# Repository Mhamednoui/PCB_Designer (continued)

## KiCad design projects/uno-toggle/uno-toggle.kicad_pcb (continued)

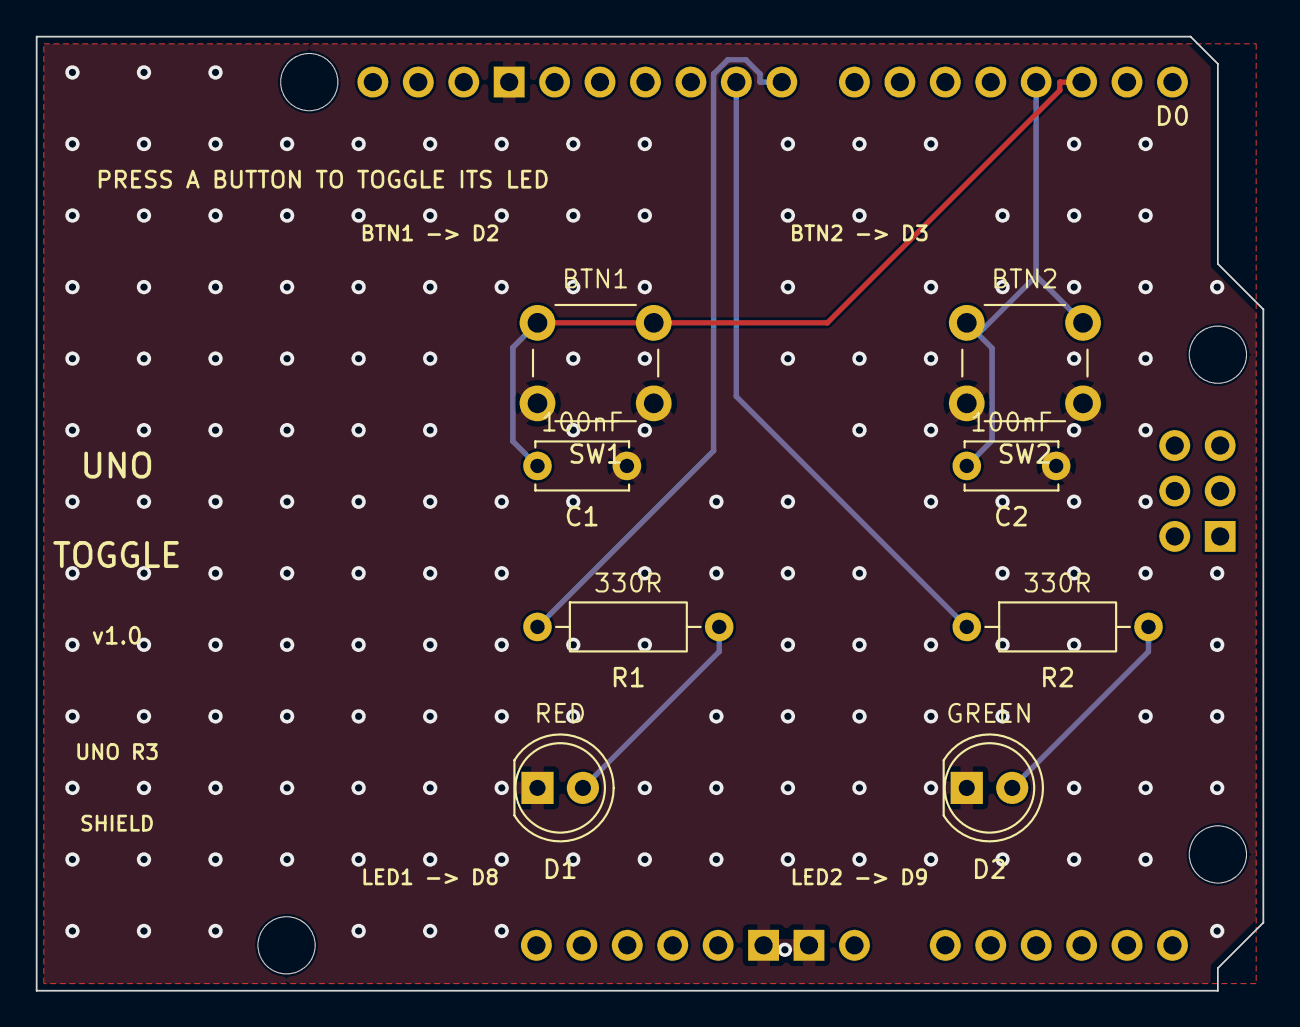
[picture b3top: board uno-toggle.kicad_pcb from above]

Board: 2 copper layers, 68.6 x 53.3 mm, 9 parts (0 on the bottom side), 7 nets.

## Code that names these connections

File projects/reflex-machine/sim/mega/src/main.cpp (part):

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
// -- LED PINS
// 74HC595 shift register driving the 7-segment digit (reuses old mux pins)
#define SEG_DATA   A0   // DS    (serial data)
#define SEG_LATCH  A1   // ST_CP (storage/latch clock)
#define SEG_CLOCK  A2   // SH_CP (shift clock)
const int LED1 = A3;   // STATE_RESET
const int LED2 = A4;   // STATE_RELEASING + last STATE_SPEED_1
const int LED3 = A5;   // STATE_RELEASING + last STATE_SPEED_2
const int LED4 = A6;   // STATE_RELEASING + last STATE_SPEED_3

// ── PWM Output Pins ───────────────────────────────────────
const uint8_t PWM_PINS[10] = { 3, 5, 6, 7, 8, 9, 10, 11, 12, 44 };
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// QC (bit 5) -> f   (top left)
// QB (bit 6) -> g   (middle)
// QA (bit 7) -> NOT CONNECTED
#define SEG_A 0b00010000  // QD bit4
#define SEG_B 0b00000010  // QG bit1
#define SEG_C 0b00000100  // QF bit2
#define SEG_D 0b00000001  // QH bit0
#define SEG_E 0b00001000  // QE bit3
#define SEG_F 0b00100000  // QC bit5
#define SEG_G 0b01000000  // QB bit6

// Common-cathode: a set bit lights its segment.
static const uint8_t SEG_DIGITS[10] = {
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  }

  // 74HC595 control pins
  pinMode(SEG_DATA,  OUTPUT);
  pinMode(SEG_CLOCK, OUTPUT);
  pinMode(SEG_LATCH, OUTPUT);
  pinMode(LED1, OUTPUT);
  pinMode(LED2, OUTPUT);
  pinMode(LED3, OUTPUT);
  pinMode(LED4, OUTPUT);
  allLedsOff();

  for (auto& b : buttons) {
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
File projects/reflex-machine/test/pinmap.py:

"""Cross-check: firmware pins  <->  PCB netlist  <->  board nets.

Reads the pin numbers straight out of the two .cpp files and compares them with gen/netlist.py,
so a wiring/firmware mismatch cannot slip through silently.
"""
import os
import re
import sys

HERE = os.path.dirname(os.path.abspath(__file__))
PRJ = os.path.dirname(HERE)
sys.path.insert(0, os.path.join(PRJ, "gen"))
import netlist as NL  # noqa: E402

MEGA_SRC = os.path.join(os.path.dirname(os.path.dirname(PRJ)), "CODES", "arduino_main_code.cpp")
ESP_SRC = os.path.join(os.path.dirname(os.path.dirname(PRJ)), "CODES", "ESP32_main_code.cpp")


def read(path):
    with open(path, encoding="utf-8", errors="replace") as f:
        return f.read()


def firmware_pins():
    src = read(MEGA_SRC)
    pins = {}
    m = re.search(r"PWM_PINS\[\d+\]\s*=\s*\{([^}]*)\}", src)
    for i, num in enumerate(n.strip() for n in m.group(1).split(",")):
        pins["MAG%d_PWM" % (i + 1)] = "D" + num
    for name, net in (("BTN_SPEED1", "BTN_S1"), ("BTN_SPEED2", "BTN_S2"), ("BTN_SPEED3", "BTN_S3"),
                      ("BTN_RESET", "BTN_RST"), ("COIN_PIN", "COIN_IN")):
        pins[net] = "D" + re.search(r"#define\s+%s\s+(\d+)" % name, src).group(1)
    for name, net in (("SEG_DATA", "SEG_DATA"), ("SEG_LATCH", "SEG_LATCH"), ("SEG_CLOCK", "SEG_CLOCK")):
        pins[net] = re.search(r"#define\s+%s\s+(A\d)" % name, src).group(1)
    for k in range(1, 5):
        pins["LED%d" % k] = re.search(r"const int LED%d\s*=\s*(A\d)" % k, src).group(1)
    pins["MEGA_TX1"] = "D18"      # Serial1 on the Mega is fixed in hardware
    pins["ESP_TX2"] = "D19"
    esp = read(ESP_SRC)
    esp_pins = {"ESP_RX2": int(re.search(r"#define\s+RX2_PIN\s+(\d+)", esp).group(1)),
                "ESP_TX2": int(re.search(r"#define\s+TX2_PIN\s+(\d+)", esp).group(1))}
    return pins, esp_pins


def board_pins():
    mega = next(p for p in NL.PARTS if p["ref"] == "A1")
    esp = next(p for p in NL.PARTS if p["ref"] == "A2")
    return ({net: pad for pad, net in mega["pins"].items()},
            {net: pad for pad, net in esp["pins"].items()})


ESP_PAD_TO_GPIO = {"25": 16, "24": 17, "6": 32, "7": 33, "8": 25, "9": 26, "10": 27, "11": 14}


def main():
    fw, fw_esp = firmware_pins()
    board, board_esp = board_pins()
    rows, bad = [], 0
    for net in sorted(fw, key=lambda n: (n.split("_")[0], n)):
        want, got = fw[net], board.get(net, "-- missing --")
        ok = want == got
        bad += not ok
        rows.append("%-12s firmware %-5s board %-12s %s" % (net, want, got, "OK" if ok else "<-- MISMATCH"))
    for net, gpio in fw_esp.items():
        pad = board_esp.get(net)
        got = ESP_PAD_TO_GPIO.get(pad)
        ok = got == gpio
        bad += not ok
        rows.append("%-12s firmware GPIO%-2s board pin %-3s (GPIO%s) %s"
                    % (net, gpio, pad, got, "OK" if ok else "<-- MISMATCH"))
    print("\n".join(rows))
    print("\n%d signals checked, %d mismatches" % (len(rows), bad))
    return 1 if bad else 0


if __name__ == "__main__":
    sys.exit(main())

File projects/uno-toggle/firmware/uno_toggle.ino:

/*
  Uno Toggle - two buttons, two LEDs.

  Press BTN1 -> LED1 toggles on/off.  Press BTN2 -> LED2 toggles on/off.

  Pin map MUST match gen/netlist.py (test/pinmap.py checks this automatically):
    BTN1 = D2   BTN2 = D3      buttons to GND, internal pull-ups => pressed reads LOW
    LED1 = D8   LED2 = D9      each via 330R to the LED anode, cathode to GND

  Debounce: the board has a 100nF across each switch, and this sketch additionally ignores any edge
  within DEBOUNCE_MS of the last accepted one. Belt and braces - mechanical switches are noisy.
*/

const uint8_t BTN1 = 2;
const uint8_t BTN2 = 3;
const uint8_t LED1 = 8;
const uint8_t LED2 = 9;

const unsigned long DEBOUNCE_MS = 25;

struct Toggle {
  uint8_t buttonPin;
  uint8_t ledPin;
  bool ledOn;
  int lastReading;
  unsigned long lastChangeMs;
};

Toggle toggles[2] = {
  { BTN1, LED1, false, HIGH, 0 },
  { BTN2, LED2, false, HIGH, 0 },
};

void setup() {
  Serial.begin(115200);
  for (Toggle &t : toggles) {
    pinMode(t.buttonPin, INPUT_PULLUP);
    pinMode(t.ledPin, OUTPUT);
    digitalWrite(t.ledPin, LOW);
    t.lastReading = digitalRead(t.buttonPin);
  }
  Serial.println(F("uno-toggle ready: press a button to toggle its LED"));
}

void loop() {
  unsigned long now = millis();

  for (Toggle &t : toggles) {
    int reading = digitalRead(t.buttonPin);

    // Falling edge = press (pull-up means idle is HIGH), and only if we've settled since the last one.
    if (reading != t.lastReading) {
      if (reading == LOW && (now - t.lastChangeMs) >= DEBOUNCE_MS) {
        t.ledOn = !t.ledOn;
        digitalWrite(t.ledPin, t.ledOn ? HIGH : LOW);
        Serial.print(F("BTN on D"));
        Serial.print(t.buttonPin);
        Serial.print(F(" -> LED on D"));
        Serial.print(t.ledPin);
        Serial.println(t.ledOn ? F(" ON") : F(" OFF"));
      }
      t.lastChangeMs = now;
      t.lastReading = reading;
    }
  }
}

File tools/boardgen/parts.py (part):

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    "id": "ne555p-dip8", "kind": "part", "mpn": "NE555P", "status": "draft", "verification": "unverified",
    "lcsc": {"id": "C46749", "class": "extended"}, "sourcing": {"stock": 1, "price_1": 0.3, "snapshot_date": "2026-01-01"},
    "package": {"name": "DIP-8", "mount": "tht"}, "kicad": {"symbol": "Timer:NE555P", "footprint": "Package_DIP:DIP-8_W7.62mm"},
    "pins": {"1": {"name": "GND", "class": "power_in"}, "2": {"name": "TRIG", "class": "input"},
             "3": {"name": "OUT", "class": "output"}, "4": {"name": "RESET", "alias": "~RST", "class": "input"},
             "5": {"name": "CONT", "class": "analog"}, "6": {"name": "THRES", "class": "input"},
             "7": {"name": "DISCH", "class": "open_collector"}, "8": {"name": "VCC", "class": "power_in"}},
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    ok(signed_hash(r) == signed_hash(shuffled), "hash stable across key order")
    ok(signed_hash(r) == signed_hash(json.loads(json.dumps(r, indent=4))), "hash stable across whitespace")
    changed = copy.deepcopy(r)
    changed["pins"]["2"]["name"], changed["pins"]["6"]["name"] = "THRES", "TRIG"
    ok(signed_hash(changed) != signed_hash(r), "hash changes when pin map changes")
    sourcing = copy.deepcopy(r)
    sourcing["sourcing"]["stock"] = 0
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       "ref-level lcsc wins over the record's; '' blanks it; None takes the record's")
    ok(registry_part("U1", "ne555p-dip8", "NE555P", {int(k): v for k, v in want.items()}, "G")["pins"] == want
       and registry_part("U1", "ne555p-dip8", "NE555P", {"gnd": "GND", "TRIG": "T", "OUT": "O", "RST": "VCC", "CONT": "CV",
                                                       "THRES": "T", "DISCH": "D", "vcc": "VCC"}, "G")["pins"] == want,
       "numeric keys, alias (RST = ~RST), and case-insensitive names all resolve")

    def raises(fn, *needles):
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    ok(raises(lambda: registry_part("U1", "ne555p-dip8", "NE555P", dict(by_name, **{"9": "X"}), "G"), "U1:", "pin 9", "neither a pad number nor a pin name"),
       "unknown pin raises, names the pin")
    ok(raises(lambda: registry_part("U1", "ne555p-dip8", "NE555P", {"GND": "GND", "VCC": "VCC"}, "G"),
              "U1:", "2 (TRIG)", "5 (CONT)", "nc=["), "unconnected pins that are not declared NC raise, naming each pad")
    ok(registry_part("U1", "ne555p-dip8", "NE555P", {"GND": "GND", "VCC": "VCC"}, "G",
                     nc=["TRIG", 3, "RESET", "CONT", "THRES", "DISCH"])["pins"] == {"1": "GND", "8": "VCC"}
       and registered_nc()["U1"] == ["2", "3", "4", "5", "6", "7"], "nc=[names or numbers] declares pins not connected")
    ok(registry_part("U1", "ne555p-dip8", "NE555P", dict(by_name, RESET=None), "G")["pins"].get("4") is None
       and registered_nc()["U1"] == ["4"], "a net of None declares that pin NC")
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        q["id"], q["pins"] = rid, {str(i + 1): {"name": n, "class": "passive"} for i, n in enumerate(order)}
        recs[rid] = q
    fn = {"E": "GND", "B": "OUT", "C": "LED_A"}
    ok(registry_part("Q1", "q-ebc", "x", fn, "G")["pins"] == {"1": "GND", "2": "OUT", "3": "LED_A"}
       and registry_part("Q1", "q-cbe", "x", fn, "G")["pins"] == {"3": "GND", "2": "OUT", "1": "LED_A"},
       "same functions on a record with another pinout renumber the pads (wrong-pinout class impossible)")

    dual = copy.deepcopy(r)                      # two pins named GND (pads 1 and 4)
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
